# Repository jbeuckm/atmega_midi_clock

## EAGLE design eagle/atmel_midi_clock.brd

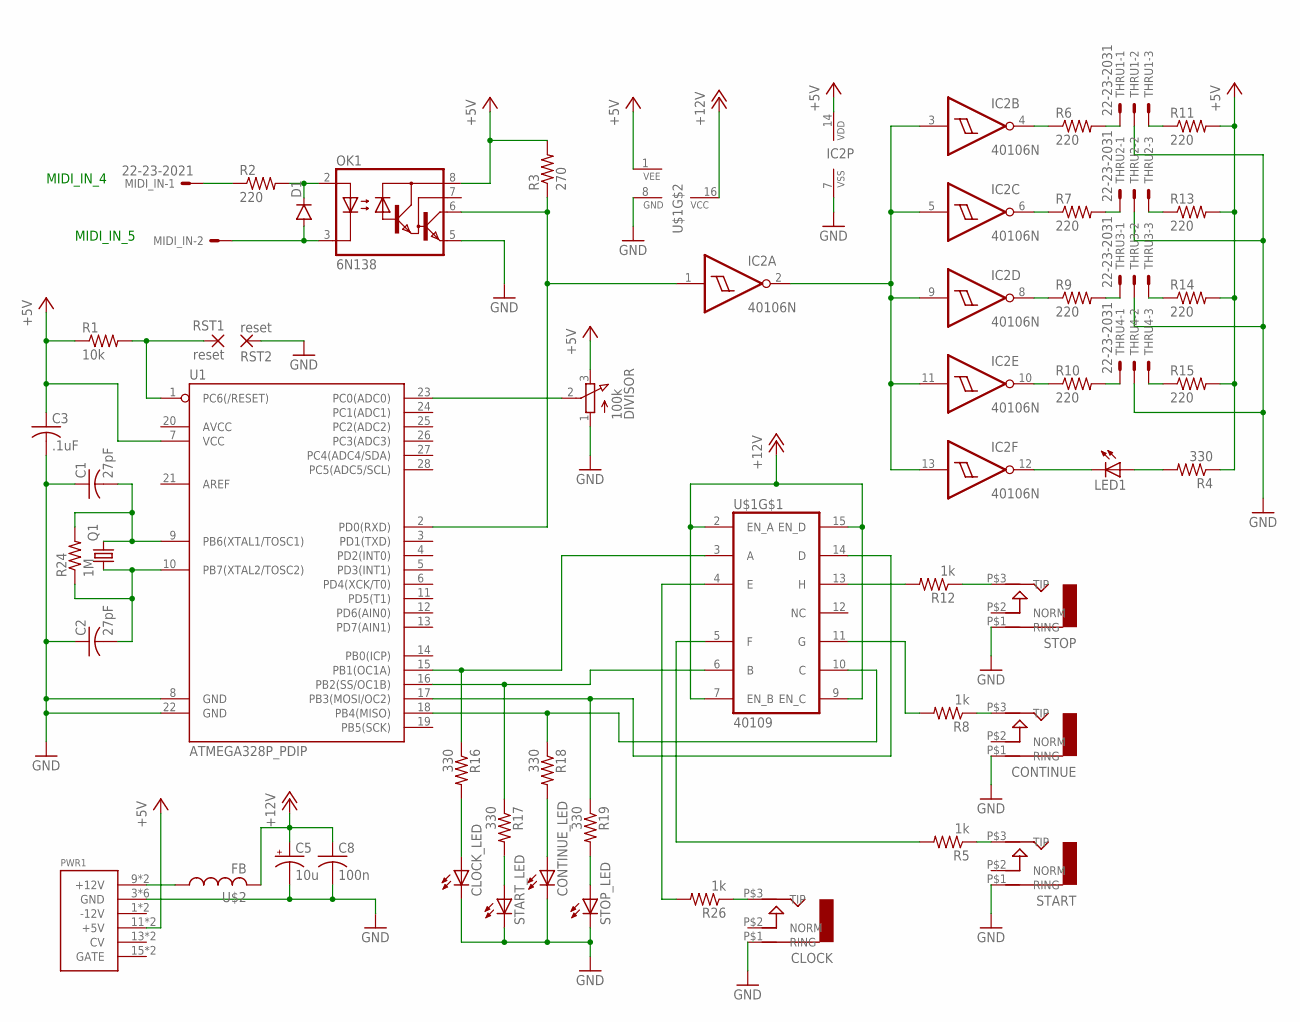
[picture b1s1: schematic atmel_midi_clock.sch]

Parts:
C1, C2: 27pF; C025-040X050
C3: .1uF; C050-024X044
C5: 10u; B45181A
C8: 100n; C050-024X044
CLOCK: AUDIO-JACK; ERTHENVAR-JACK-90DEG
CLOCK_LED: LED5MM
CONTINUE: AUDIO-JACK; ERTHENVAR-JACK-90DEG
CONTINUE_LED: LED5MM
D1: DIODE1N4148; DIODE-1N4148
DIVISOR: 100k; 3RP/1610N
IC2: 40106N; DIL14
LED1: LED5MM
MIDI_IN: 22-23-2021
OK1: 6N138; DIL08
PWR1: POWER; POWER_16
Q1: CRYSTALHC49S; HC49/S
R1: 10k; 0207/10
R2, R6, R7, R9, R10, R11, R13, R14, R15: 220; 0207/10
R3: 270; 0207/10
R4, R16, R17, R18, R19: 330; 0207/10
R5, R8, R12, R26: 1k; 0207/10
R24: 1M; 0207/10
RST1, RST2: reset; 2,54/0,9
START: AUDIO-JACK; ERTHENVAR-JACK-90DEG
START_LED: LED5MM
STOP: AUDIO-JACK; ERTHENVAR-JACK-90DEG
STOP_LED: LED5MM
THRU1, THRU2, THRU3, THRU4: 22-23-2031
U1: ATMEGA328P_PDIP; DIL28-3
U$1: 40109; DIL16
U$2: FB

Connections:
+5V: C3.1, DIVISOR.3 (E), IC2.14 (VDD), OK1.8 (VCC), PWR1.11 (+5V), PWR1.12 (+5V), R1.1, R3.2, R4.1, R11.2, R13.2, R14.2, R15.2, U1.7 (VCC), U$1.1 (VEE)
+12V: C5.+, C8.1, U$1.2 (EN_A), U$1.7 (EN_B), U$1.9 (EN_C), U$1.15 (EN_D), U$1.16 (VCC), U$2.P$2 (2)
GND: C1.1, C2.1, C3.2, C5.-, C8.2, CLOCK.P$1 (RING), CLOCK_LED.K (C), CONTINUE.P$1 (RING), CONTINUE_LED.K (C), DIVISOR.1 (A), IC2.7 (VSS), OK1.5 (GND), PWR1.3 (GND), PWR1.4 (GND), PWR1.5 (GND), PWR1.6 (GND), PWR1.7 (GND), PWR1.8 (GND), RST2.1, START.P$1 (RING), START_LED.K (C), STOP.P$1 (RING), STOP_LED.K (C), THRU1.2, THRU2.2, THRU3.2, THRU4.2, U1.8 (GND), U1.22 (GND), U$1.8 (GND)
unnamed: R18.1, U1.18 (PB4(MISO)), U$1.10 (C)
unnamed: R5.1, START.P$3 (TIP)
unnamed: D1.A, MIDI_IN.2, OK1.3 (C)
unnamed: C1.2, Q1.2, R24.2, U1.9 (PB6(XTAL1/TOSC1))
unnamed: C2.2, Q1.1, R24.1, U1.10 (PB7(XTAL2/TOSC2))
unnamed: R19.1, U1.17 (PB3(MOSI/OC2)), U$1.14 (D)
unnamed: D1.C, OK1.2 (A), R2.2
unnamed: MIDI_IN.1, R2.1
unnamed: R16.1, U1.15 (PB1(OC1A)), U$1.3 (A)
unnamed: R17.1, U1.16 (PB2(SS/OC1B)), U$1.6 (B)
unnamed: PWR1.9 (+12V), PWR1.10 (+12V), U$2.P$1 (1)
unnamed: R5.2, U$1.5 (F)
unnamed: CONTINUE.P$3 (TIP), R8.1
unnamed: R26.2, U$1.4 (E)
unnamed: R12.2, U$1.13 (H)
unnamed: R8.2, U$1.11 (G)
unnamed: IC2.2 (O), IC2.3 (I), IC2.5 (I), IC2.9 (I), IC2.11 (I), IC2.13 (I)
unnamed: R12.1, STOP.P$3 (TIP)
unnamed: DIVISOR.2 (S), U1.23 (PC0(ADC0))
unnamed: IC2.12 (O), LED1.K (C)
unnamed: LED1.A, R4.2
unnamed: IC2.4 (O), R6.1
unnamed: IC2.6 (O), R7.1
unnamed: IC2.8 (O), R9.1
unnamed: IC2.10 (O), R10.1
unnamed: R6.2, THRU1.1
unnamed: R7.2, THRU2.1
unnamed: R9.2, THRU3.1
unnamed: IC2.1 (I), OK1.6 (VO), R3.1, U1.2 (PD0(RXD))
unnamed: CLOCK.P$3 (TIP), R26.1
unnamed: R10.2, THRU4.1
unnamed: R11.1, THRU1.3
unnamed: R13.1, THRU2.3
unnamed: R14.1, THRU3.3
unnamed: R15.1, THRU4.3
unnamed: R17.2, START_LED.A
unnamed: CLOCK_LED.A, R16.2
unnamed: CONTINUE_LED.A, R18.2
unnamed: R19.2, STOP_LED.A
unnamed: R1.2, RST1.1, U1.1 (PC6(/RESET))

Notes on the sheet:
MIDI_IN_4
MIDI_IN_5

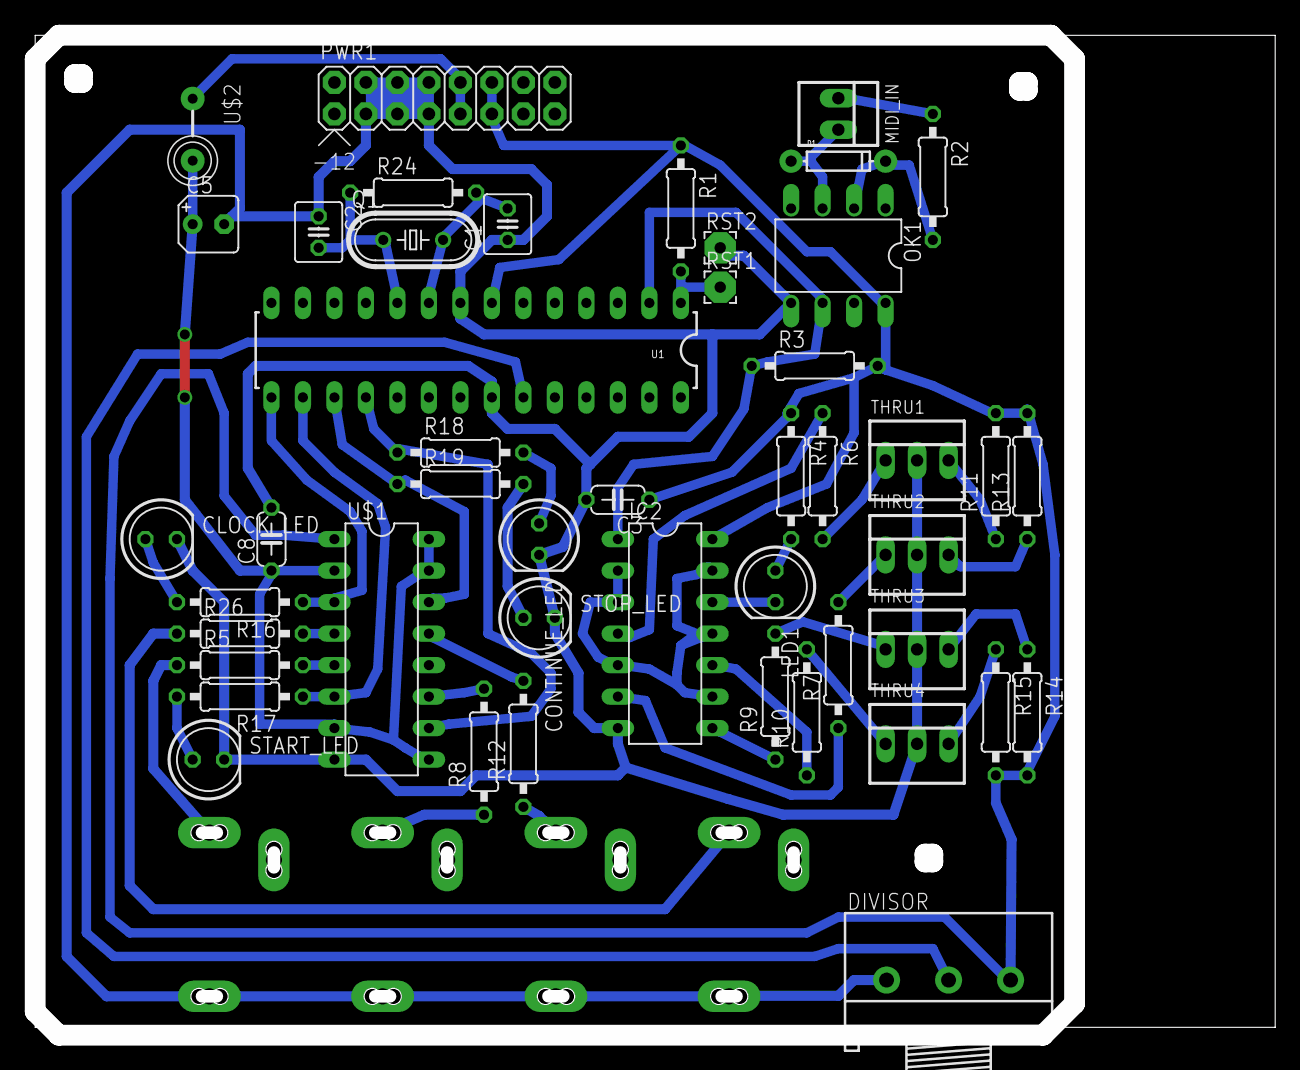
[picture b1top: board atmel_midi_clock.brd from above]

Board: 2 copper layers, 99.2 x 80.6 mm, 51 parts (0 on the bottom side), 43 nets.

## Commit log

2016-02-09 midi thrus and leds
2016-02-09 layout begins
2016-02-09 almost routed
2016-02-09 routed
2016-02-09 route tweaks
2016-02-10 gcode
2016-02-11 first cut happened and arduino code implemented
2016-02-12 working and now with set clock divisor options
2016-02-16 panel been cut

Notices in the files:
parts and their libraries:
SparkFun-DiscreteSemi: Licensing: Creative Commons ShareAlike 4.0 International - https://creativecommons.org/licenses/by-sa/4.0
